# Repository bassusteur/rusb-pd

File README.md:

# Radio USB-PD
Giving a modern touch to my SWL receiver made by Yaesu, the FRG7700, i came up with this idea while i was looking at the manual and noticed there was a "DC Power mod" available for the radio.
The parts for this aren't being sold much anymore, all i could find was a listing on ebay and it cost about 36 dollars for the whole kit + 30 dollars more to ship to EU.
The final result is these two boards, i figured there wasn't much space inside the chassis for an additional board but i did what i could, the first features a vertical usb-c connector and is made so it can be mounted to the chassis connecting to the other board with 90 degree headers.
The second board features a microcontroller (CH32V003), pd controller (FUSB302) and a pi filter for filtering out any noise incoming from the external psu.

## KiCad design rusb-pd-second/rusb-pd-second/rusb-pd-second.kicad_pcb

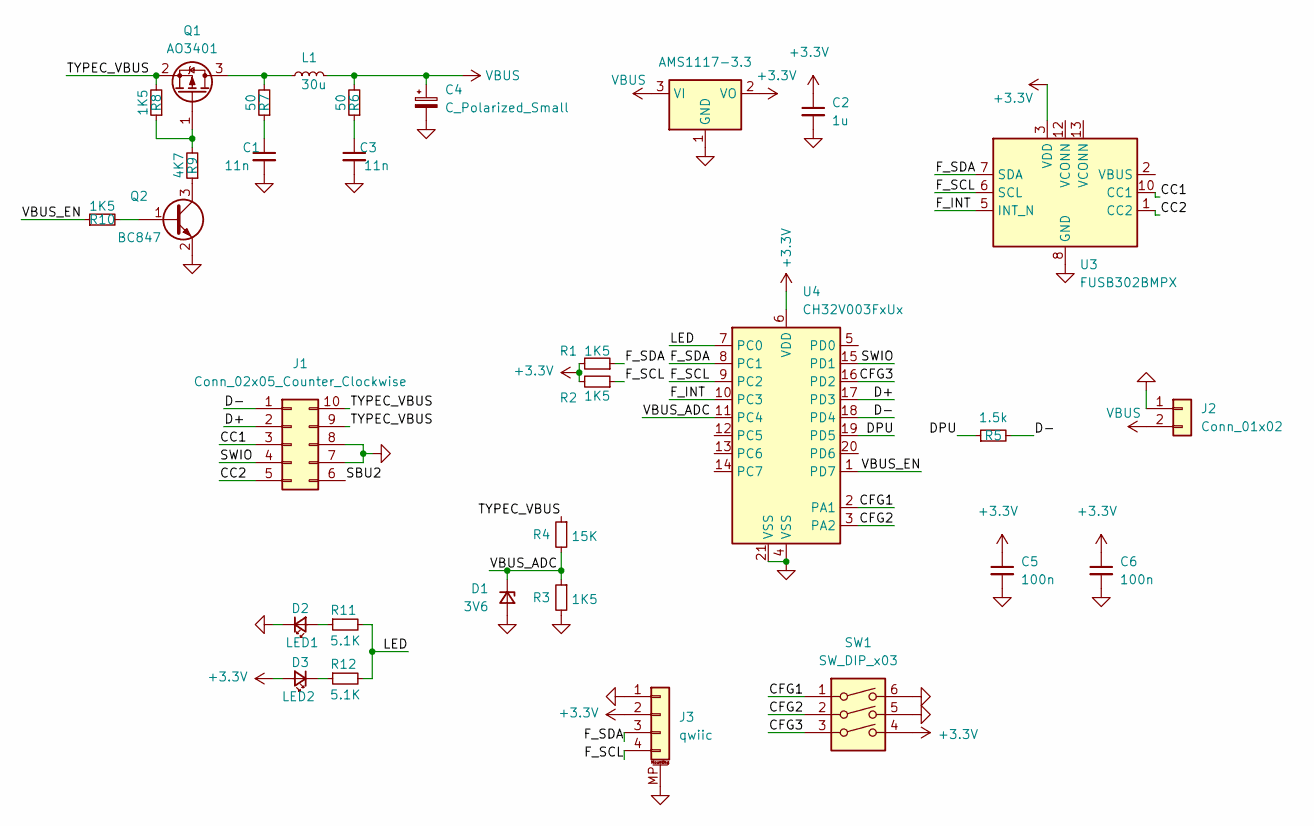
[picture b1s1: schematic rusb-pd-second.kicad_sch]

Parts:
C1, C3: 11n; C_0805_2012Metric
C2: 1u; C_0603_1608Metric
C4: C_Polarized_Small; CP_Radial_D4.0mm_P2.00mm
C5, C6: 100n; C_0603_1608Metric
D1: 3V6; D_0805_2012Metric
D2: LED1; LED_0603_1608Metric
D3: LED2; LED_0603_1608Metric
J1: Conn_02x05_Counter_Clockwise; PinSocket_2x05_P2.54mm_Vertical
J2: Conn_01x02; PinSocket_1x02_P2.54mm_Vertical
J3: qwiic; JST_SH_SM04B-SRSS-TB_1x04-1MP_P1.00mm_Horizontal
L1: 30u; IND-SMD_L6.0-W6.0_FNR60XXS
Q1: AO3401; SOT-23
Q2: BC847; SOT-23
R1, R2, R3, R8, R10: 1K5; R_0402_1005Metric
R4: 15K; R_0402_1005Metric
R5: 1.5k; R_0402_1005Metric
R6, R7: 50; R_0402_1005Metric
R9: 4K7; R_0402_1005Metric
R11, R12: 5.1K; R_0402_1005Metric
SW1: SW_DIP_x03; SW-SMD_6P-P1.27_EU-03KS
U1: AMS1117-3.3; SOT-223-3_TabPin2
U3: FUSB302BMPX; WQFN-14-1EP_2.5x2.5mm_P0.5mm_EP1.45x1.45mm
U4: CH32V003FxUx; QFN-20-1EP_3x3mm_P0.4mm_EP1.65x1.65mm

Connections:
+3.3V: C2.1, C5.1, C6.1, D3.2 (A), J3.2, R1.2, R2.2, SW1.4, U1.2 (VO), U3.3 (VDD), U3.4 (VDD), U4.6 (VDD)
/CC1: J1.3, U3.10 (CC1), U3.11 (CC1)
/CC2: J1.5, U3.1 (CC2), U3.14 (CC2)
/CFG1: SW1.1, U4.2 (PA1)
/CFG2: SW1.2, U4.3 (PA2)
/CFG3: SW1.3, U4.16 (PD2)
/D+: J1.2, U4.17 (PD3)
/D-: J1.1, R5.2, U4.18 (PD4)
/DPU: R5.1, U4.19 (PD5)
/F_INT: U3.5 (INT_N), U4.10 (PC3)
/F_SCL: J3.4, R2.1, U3.6 (SCL), U4.9 (PC2)
/F_SDA: J3.3, R1.1, U3.7 (SDA), U4.8 (PC1)
/LED: R11.2, R12.2, U4.7 (PC0)
/SBU2: J1.6
/SWIO: J1.4, U4.15 (PD1)
/TYPEC_VBUS: J1.9, J1.10, Q1.2 (S), R4.1, R8.2
/VBUS_ADC: D1.1 (K), R3.1, R4.2, U4.11 (PC4)
/VBUS_EN: R10.1, U4.1 (PD7)
GND: C1.2, C2.2, C3.2, C4.2, C5.2, C6.2, D1.2 (A), D2.1 (K), J1.7, J1.8, J2.1, J3.1, J3.MP (MountPin), Q2.2 (E), R3.2, SW1.5, SW1.6, U1.1 (GND), U3.8 (GND), U3.9 (GND), U3.15 (GND), U4.4 (VSS), U4.21 (VSS)
unnamed: C1.1, R7.1
unnamed: C3.1, R6.1
unnamed: D2.2 (A), R11.1
unnamed: D3.1 (K), R12.1
unnamed: L1.1, Q1.3 (D), R7.2
unnamed: Q1.1 (G), R8.1, R9.2
unnamed: Q2.1 (B), R10.2
unnamed: Q2.3 (C), R9.1
VBUS: C4.1, J2.2, L1.2, R6.2, U1.3 (VI)

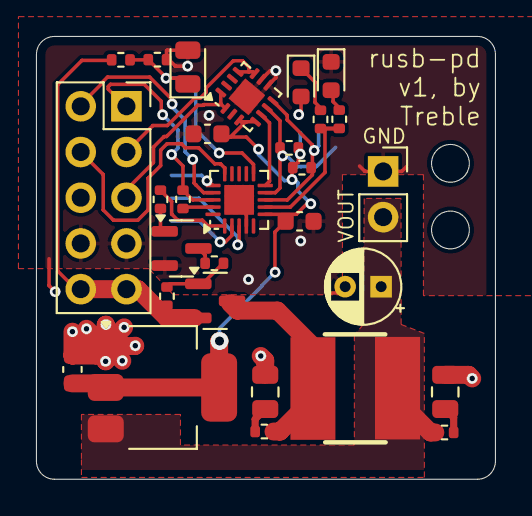
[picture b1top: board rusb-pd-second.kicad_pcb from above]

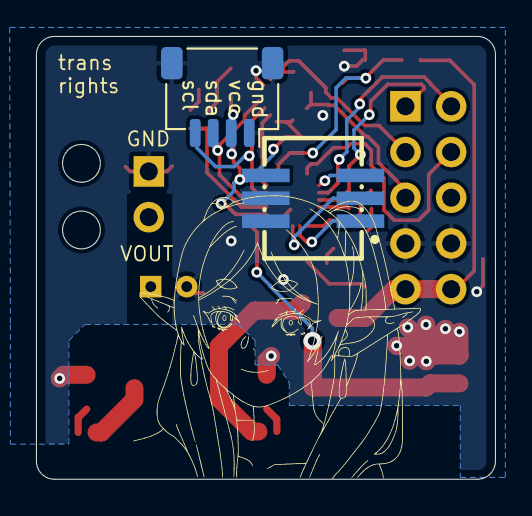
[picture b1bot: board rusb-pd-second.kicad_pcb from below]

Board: 2 copper layers, 25.5 x 24.6 mm, 31 parts (2 on the bottom side), 27 nets.

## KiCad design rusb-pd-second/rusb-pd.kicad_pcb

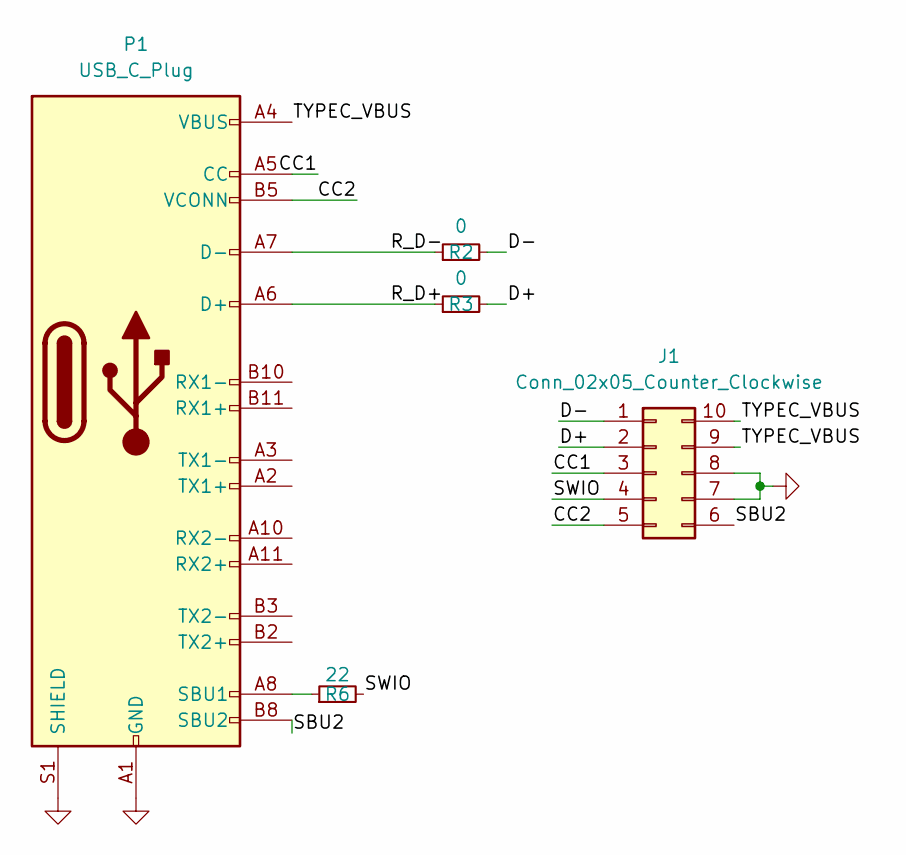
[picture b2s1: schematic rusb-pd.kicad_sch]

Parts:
J1: Conn_02x05_Counter_Clockwise; PinSocket_2x05_P2.54mm_Vertical
P1: USB_C_Plug; USB_C_Receptacle_GCT_USB4115-03-C
R2, R3: 0; R_0402_1005Metric
R6: 22; R_0402_1005Metric

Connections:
/CC1: J1.3, P1.A5 (CC)
/CC2: J1.5, P1.B5 (VCONN)
/D+: J1.2, R3.2
/D-: J1.1, R2.2
/R_D+: P1.A6 (D+), R3.1
/R_D-: P1.A7 (D-), R2.1
/SBU2: J1.6, P1.B8 (SBU2)
/SWIO: J1.4, R6.2
/TYPEC_VBUS: J1.9, J1.10, P1.A4 (VBUS), P1.A9 (VBUS), P1.B4 (VBUS), P1.B9 (VBUS)
GND: J1.7, J1.8, P1.A1 (GND), P1.A12 (GND), P1.B1 (GND), P1.B12 (GND), P1.S1 (SHIELD)
unnamed: P1.A8 (SBU1), R6.1

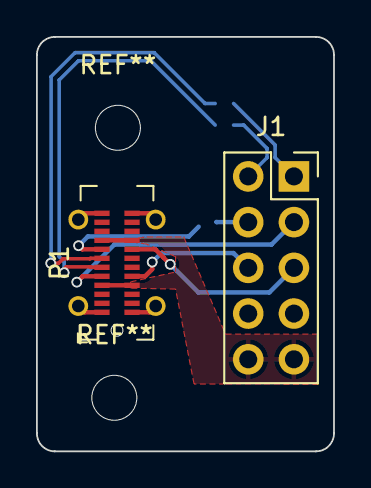
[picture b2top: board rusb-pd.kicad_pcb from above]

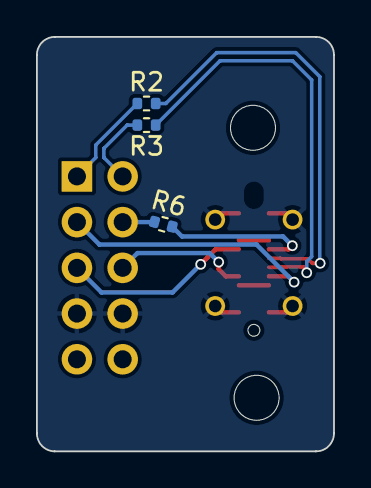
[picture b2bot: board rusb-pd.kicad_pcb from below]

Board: 2 copper layers, 16.5 x 23.0 mm, 5 parts (3 on the bottom side), 11 nets.

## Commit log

2024-09-03 lotta changes (described in the articel)
